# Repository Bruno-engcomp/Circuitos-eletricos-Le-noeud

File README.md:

Aqui será um README bonito no futuro

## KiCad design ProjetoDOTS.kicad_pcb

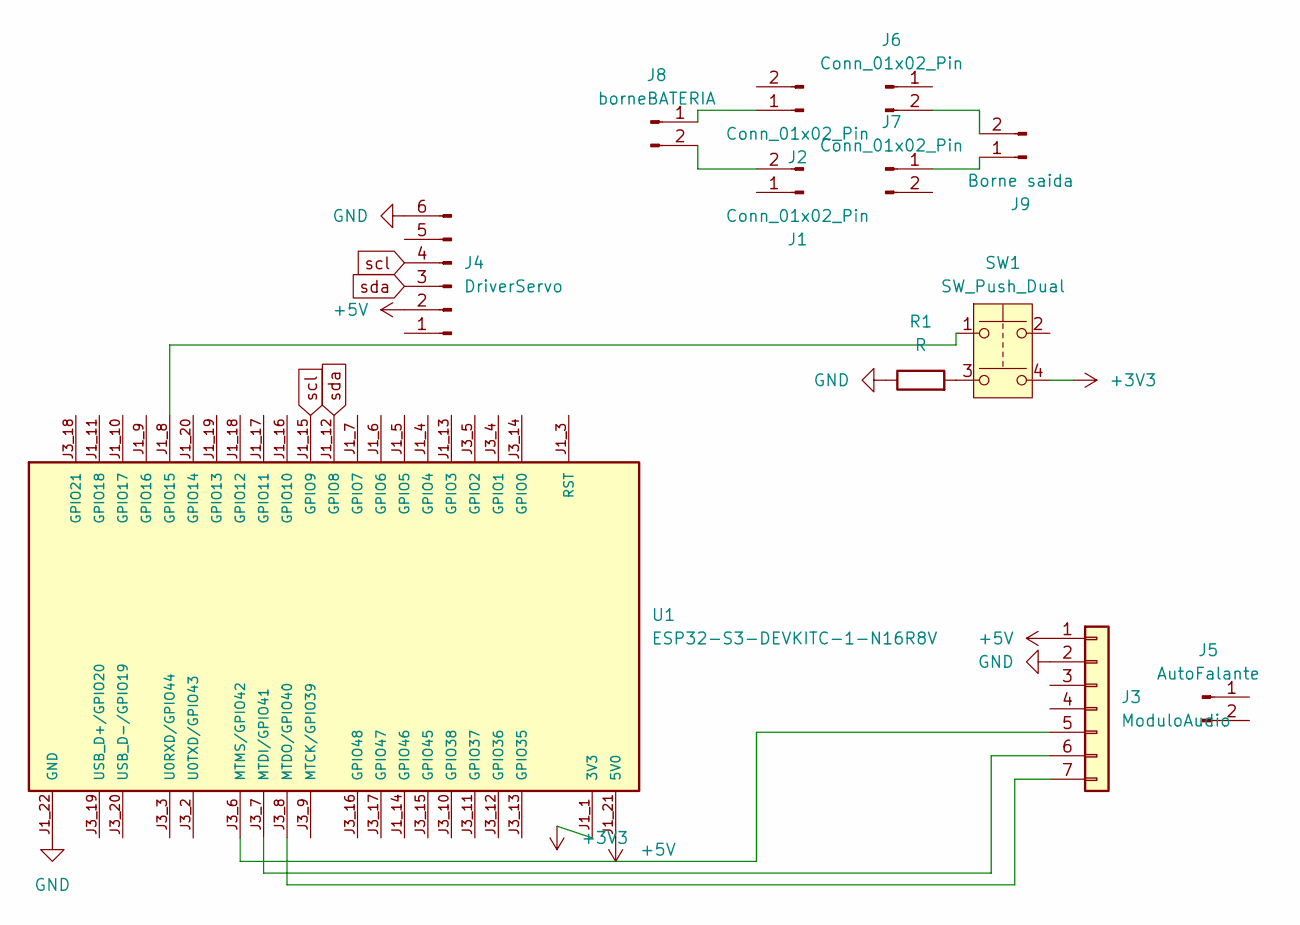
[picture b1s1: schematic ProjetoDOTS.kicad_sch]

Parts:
J1, J2, J6, J7: Conn_01x02_Pin; PinHeader_1x02_P2.54mm_Vertical
J3: ModuloAudio; PinHeader_1x07_P2.54mm_Vertical
J4: DriverServo; PinHeader_1x06_P2.54mm_Vertical
J5: AutoFalante; PinHeader_1x02_P2.54mm_Vertical
J8: borneBATERIA; PinHeader_1x02_P2.54mm_Vertical
J9: Borne saida; PinHeader_1x02_P2.54mm_Vertical
R1: R; R_Axial_DIN0207_L6.3mm_D2.5mm_P10.16mm_Horizontal
SW1: SW_Push_Dual; Push_E-Switch_KS01Q01
U1: ESP32-S3-DEVKITC-1-N16R8V; XCVR_ESP32-S3-DEVKITC-1-N16R8V; PARTREV 1.1

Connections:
+3V3: SW1.4, U1.J1_1 (3V3), U1.J1_2 (3V3)
+5V: J3.1, J4.2, U1.J1_21 (5V0)
GND: J3.2, J4.6, R1.1, U1.J1_22 (GND), U1.J3_1 (GND), U1.J3_21 (GND), U1.J3_22 (GND)
unnamed: J1.2 (Pin_2_2), J8.2
unnamed: J2.1 (Pin_1_1), J8.1
unnamed: J3.5, U1.J3_6 (MTMS/GPIO42)
unnamed: J3.6, U1.J3_7 (MTDI/GPIO41)
unnamed: J3.7, U1.J3_8 (MTDO/GPIO40)
unnamed: J6.2 (Pin_2_2), J9.2
unnamed: J7.1 (Pin_1_1), J9.1
unnamed: R1.2, SW1.3
unnamed: SW1.1, U1.J1_8 (GPIO15)
scl: J4.4, U1.J1_15 (GPIO9)
sda: J4.3, U1.J1_12 (GPIO8)

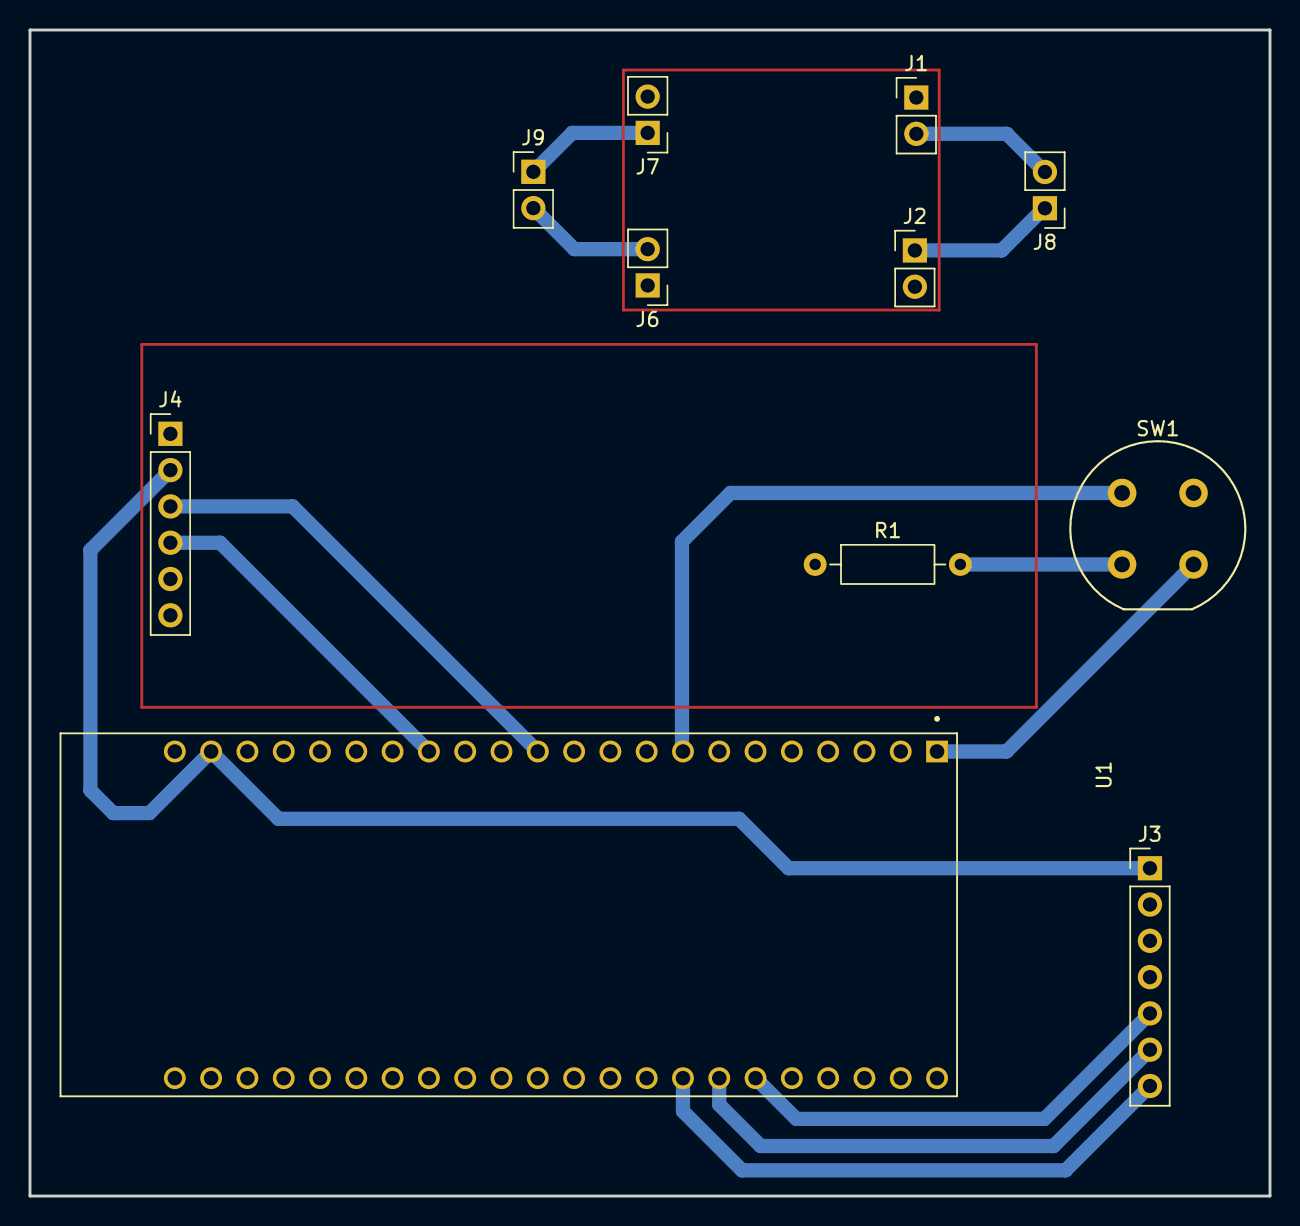
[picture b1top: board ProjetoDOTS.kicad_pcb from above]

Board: 2 copper layers, 86.8 x 81.6 mm, 11 parts (0 on the bottom side), 14 nets.

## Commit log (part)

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2026-06-10 Primeiro Commit -Adição de um arquito de teste para servos com letras A e B
2026-06-10 Alteração da Lib para a versão do esp32
2026-06-10 -Main cpp
2026-06-10 Main
2026-06-10 Platform IO adicionado ao projeto
2026-06-10 Pasta nova para dos arquivos .cpp
2026-06-10 Alfabeto feito em valores de true ou false
2026-06-11 -Adição de função para converter char para o endereço no array -TODO conveter o aúdio para char futuramente com a entrada - Pesquisar a lib de aúdio
2026-06-11 -Correção de alguns erros de sintaxe -Alfabeto com 26 letras
2026-06-12 -Diagrama de componentes em arquivo json
2026-06-12 -Adição do arquivo .ino do projeto
2026-06-12 First
2026-06-12 -Audios que serão armazenados no cartão microSD
2026-06-18 - Main.ino com o código do main.cpp
2026-06-27 - Mudança dos pinos conforme o nosso esp32 - Botão de confirmação funcionando - Pinos subindo ao mesmo tempo - Pinos abaixando ao mesmo tempo com delay de um segundo - Aúdios no github
2026-06-28 Rename A.mp3 to 0001.mp3
2026-06-28 Rename B.mp3 to 0002.mp3
2026-06-28 Rename C.mp3 to 0003.mp3
2026-06-28 Rename D.mp3 to 0004.mp3
2026-06-28 Rename E.mp3 to 0005.mp3
2026-06-28 Rename F.mp3 to 0006.mp3
2026-06-28 Rename G.mp3 to 0007.mp3
2026-06-28 Rename H.mp3 to 0008.mp3
2026-06-28 Rename I.mp3 to 0009.mp3
2026-06-28 Rename J.mp3 to 0010.mp3
2026-06-28 Rename K.mp3 to 0011.mp3
2026-06-28 Rename L.mp3 to 0012.mp3
2026-06-28 Rename M.mp3 to 0013.mp3
2026-06-28 Rename N.mp3 to 0014.mp3
2026-06-28 Rename O.mp3 to 0015.mp3
2026-06-28 Rename P.mp3 to 0016.mp3
2026-06-28 Rename Q.mp3 to 0017.mp3
2026-06-28 Rename R.mp3 to 0018.mp3
2026-06-28 Rename S.mp3 to 0019.mp3
2026-06-28 Rename T.mp3 to 0020.mp3
2026-06-28 Rename U.mp3 to 0021.mp3
2026-06-28 Rename V.mp3 to 0022.mp3
2026-06-28 Rename W.mp3 to 0023.mp3
2026-06-28 Rename X.mp3 to 0024.mp3
2026-06-28 Rename Y.mp3 to 0025.mp3
2026-06-28 Rename Z.mp3 to 0026.mp3
